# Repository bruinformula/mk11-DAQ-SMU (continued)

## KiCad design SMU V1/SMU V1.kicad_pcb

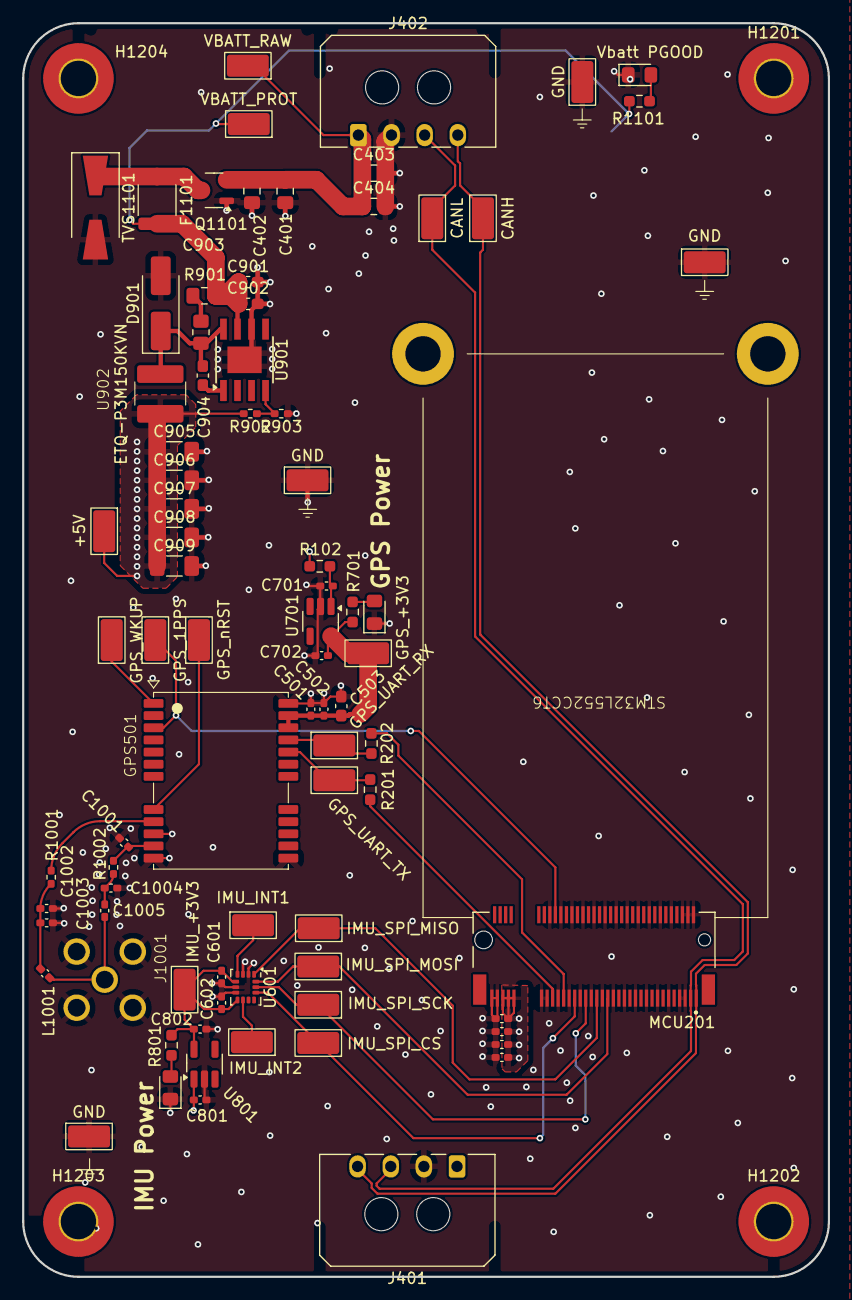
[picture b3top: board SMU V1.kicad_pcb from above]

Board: 4 copper layers, 72.9 x 113.5 mm, 86 parts (0 on the bottom side), 35 nets.

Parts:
C201, C202, C203, C204, C502, C601, C602, C1002: 100n; C_0402_1005Metric_Pad0.74x0.62mm_HandSolder
C401, C402, C403, C404: 22u; C_0805_2012Metric_Pad1.18x1.45mm_HandSolder
C501: 33p; C_0402_1005Metric_Pad0.74x0.62mm_HandSolder
C503: 4.7u; C_0603_1608Metric_Pad1.08x0.95mm_HandSolder
C701, C702, C801, C802: 2.2u; C_0402_1005Metric_Pad0.74x0.62mm_HandSolder
C901, C902: 22u; C_0603_1608Metric_Pad1.08x0.95mm_HandSolder
C903: 1.8p; C_0805_2012Metric_Pad1.18x1.45mm_HandSolder
C904: 10n; C_0603_1608Metric_Pad1.08x0.95mm_HandSolder
C905, C906, C907, C908, C909: 100u; C_1206_3216Metric_Pad1.33x1.80mm_HandSolder
C1001, C1003, C1004, C1005: 100p; C_0402_1005Metric_Pad0.74x0.62mm_HandSolder
D701, D801: GPS Power; D_0805_2012Metric_Pad1.15x1.40mm_HandSolder
D901: 550m; D_SMA_Handsoldering
D1101: Vbatt PGOOD; D_0805_2012Metric_Pad1.15x1.40mm_HandSolder
F1101: 500mA; Fuse_1812_4532Metric
GPS501: LC29HEAMD; Quectel LC49
H1201, H1202, H1203, H1204: MountingHole_Pad; MountingHole_3.2mm_M3_Pad_TopBottom
J401, J402: Connector; Molex_Micro-Fit_3.0_43650-0400_1x04_P3.00mm_Horizontal
J1001: SMA; THT SMA
L1001: 68n; L_0402_1005Metric_Pad0.77x0.64mm_HandSolder
MCU201: Krill; TE_1-2199119-5
Q1101: SI2301CDS-T1-GE3; SOT-23-3
R102, R201, R202: 0; R_0603_1608Metric_Pad0.98x0.95mm_HandSolder
R701, R801: 120; R_0603_1608Metric_Pad0.98x0.95mm_HandSolder
R901: 180k; R_0805_2012Metric_Pad1.20x1.40mm_HandSolder
R902: 10k; R_0402_1005Metric_Pad0.72x0.64mm_HandSolder
R903: 3.3k; R_0402_1005Metric_Pad0.72x0.64mm_HandSolder
R1001: 10; R_0402_1005Metric_Pad0.72x0.64mm_HandSolder
R1002: 0; R_0402_1005Metric_Pad0.72x0.64mm_HandSolder
R1101: 1.8k; R_0603_1608Metric_Pad0.98x0.95mm_HandSolder
TP205: CANH; TestPoint_Keystone_5019_Miniature
TP206: CANL; TestPoint_Keystone_5019_Miniature
TP301: VBATT_RAW; TestPoint_Keystone_5019_Miniature
TP302: VBATT_PROT; TestPoint_Keystone_5019_Miniature
TP303: +5V; TestPoint_Keystone_5019_Miniature
TP305, TP306, TP307, TP308: GND; TestPoint_Keystone_5019_Miniature
TP501: GPS_UART_RX; TestPoint_Keystone_5019_Miniature
TP502: GPS_UART_TX; TestPoint_Keystone_5019_Miniature
TP503: GPS_WKUP; TestPoint_Keystone_5019_Miniature
TP504: GPS_1PPS; TestPoint_Keystone_5019_Miniature
TP505: GPS_nRST; TestPoint_Keystone_5019_Miniature
TP506: GPS_+3V3; TestPoint_Keystone_5019_Miniature
TP601: IMU_+3V3; TestPoint_Keystone_5019_Miniature
TP602: IMU_INT2; TestPoint_Keystone_5019_Miniature
TP603: IMU_INT1; TestPoint_Keystone_5019_Miniature
TP604: IMU_SPI_CS; TestPoint_Keystone_5019_Miniature
TP605: IMU_SPI_MISO; TestPoint_Keystone_5019_Miniature
TP606: IMU_SPI_MOSI; TestPoint_Keystone_5019_Miniature
TP607: IMU_SPI_SCK; TestPoint_Keystone_5019_Miniature
TVS1101: 16Vrwm; D_SMA-SMB_Universal_Handsoldering
U601: LSM6DSOTR; LGA-14_3x2.5mm_P0.5mm_LayoutBorder3x4y
U701, U801: TPS7A2033PDBVR; SOT-23-5_HandSoldering
U901: TPS5430DDAR; TI_SO-PowerPAD-8
U902: ETQ-P3M150KVN; BWVS005050404R7M00

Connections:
+5V: C201.1, C202.1, C203.1, C204.1, C801.1, C905.1, C906.1, C907.1, C908.1, C909.1, MCU201.67 (5V), MCU201.69 (5V), MCU201.71 (5V), R102.2, R902.2, TP303.1, U801.1 (VIN), U902.2
/Antenna/ANT_OUT_RF: C1005.2, J1001.1, L1001.1
/Antenna/GPS_ANT_RF: C1001.1, GPS501.11 (RF_IN), R1002.1
/Antenna/GPS_ANT_RF_R: C1004.1, C1005.1, R1002.2
/Antenna/GPS_RF_VDD: GPS501.9 (VDD_RF), R1001.1
/Antenna/GPS_RF_VDD_R: C1002.1, C1003.1, L1001.2, R1001.2
/CAN+: J401.4 (CANH), J402.4 (CANH), MCU201.1 (MCU_CAN+), TP205.1
/CAN-: J401.3 (CANL), J402.3 (CANL), MCU201.3 (MCU_CAN-), TP206.1
/GPS/GPS_1PPS: GPS501.3 (1PPS), MCU201.52 (PB0), TP504.1
/GPS/GPS_UART.RX: GPS501.21 (UART_RXD), R202.2, TP501.1
/GPS/GPS_UART.TX: GPS501.20 (UART_TXD), R201.2, TP502.1
/GPS/GPS_WKUP: GPS501.1 (WAKEUP), TP503.1
/GPS/GPS_nRST: GPS501.8 (RESET_N), TP505.1
/GPS/PP3300_GPS_VCC: C501.1, C502.1, C503.1, C702.1, GPS501.22 (V_BCKUP), GPS501.23 (VCC), R701.1, TP506.1, U701.5 (VOUT)
/GPS/PP5000_GPS_VSUPP: C701.1, R102.1, U701.1 (VIN)
/IMU/IMU_INT1: TP603.1, U601.4 (INT1)
/IMU/IMU_INT2: TP602.1, U601.9 (INT2)
/IMU/PP3300_IMU_VDD: C601.1, C602.1, C802.1, R801.1, TP601.1, U601.5 (VDDIO), U601.8 (VDD), U801.5 (VOUT)
/IMU_SPI.CS: MCU201.45 (SPI1_NSS), TP604.1, U601.12 (CS)
/IMU_SPI.MISO: MCU201.37 (SPI1_MISO), TP605.1, U601.1 (SPI_MISO)
/IMU_SPI.MOSI: MCU201.33 (SPI1_MOSI), TP606.1, U601.14 (4W_SPI_MOSI)
/IMU_SPI.SCK: MCU201.41 (SPI1_SCK), TP607.1, U601.13 (SPI_SCK)
/Main IO/VBATT+: C401.1, C402.1, C403.1, C404.1, J401.1 (VBATT+), J402.1 (VBATT+), Q1101.2 (S), TP301.1
/Power/5V Buck/BUCK_VSENSE: R902.1, R903.2, U901.4 (VSENSE)
/Power/5V Buck/PPVAR_VBATT_PROT: C901.1, C902.1, C903.1, F1101.2, R1101.1, TP302.1, U901.7 (VIN)
/Power/5V Buck/Rsnub: C903.2, R901.1
/Power/5V Buck/SWITCH_NODE: C904.2, D901.1 (K), R901.2, U901.8 (PH), U902.1
GND: C201.2, C202.2, C203.2, C204.2, C401.2, C402.2, C403.2, C404.2, C501.2, C502.2, C503.2, C601.2, C602.2, C701.2, C702.2, C801.2, C802.2, C901.2, C902.2, C905.2, C906.2, C907.2, C908.2, C909.2, C1001.2, C1002.2, C1003.2, C1004.2, D701.1 (K), D801.1 (K), D901.2 (A), D1101.1 (K), GPS501.10 (GND), GPS501.12 (GND), GPS501.13 (GND), GPS501.24 (GND), J401.2 (GND), J402.2 (GND), J1001.2, MCU201.2 (GND), MCU201.4 (GND), MCU201.5 (GND), MCU201.6 (GND), MCU201.7 (GND), MCU201.10 (GND), MCU201.11 (GND), MCU201.14 (GND), MCU201.15 (GND), MCU201.18 (GND), MCU201.19 (GND), MCU201.22 (GND), MCU201.23 (GND), MCU201.26 (GND), MCU201.27 (GND), MCU201.30 (GND), MCU201.31 (GND), MCU201.34 (GND), MCU201.35 (GND), MCU201.38 (GND), MCU201.39 (GND), MCU201.42 (GND), MCU201.43 (GND), MCU201.46 (GND), MCU201.47 (GND), MCU201.50 (GND), MCU201.51 (GND), MCU201.54 (GND), MCU201.55 (GND), MCU201.57 (GND), MCU201.73 (GND), MCU201.75 (GND), Q1101.1 (G), R903.1, TP305.1, TP306.1, TP307.1, TP308.1, TVS1101.2, U601.2 (SDx), U601.3 (SCx), U601.6 (GND), U601.7 (GND), U701.2 (GND), U801.2 (GND), U901.6 (GND), U901.9 (GNDPAD)
unnamed: D701.2 (A), R701.2
unnamed: D801.2 (A), R801.2
unnamed: D1101.2 (A), R1101.2
unnamed: MCU201.53 (UART4_TX), R201.1
unnamed: MCU201.49 (UART4_RX), R202.1
unnamed: F1101.1, Q1101.3 (D), TVS1101.1
unnamed: C904.1, U901.1 (BOOT)

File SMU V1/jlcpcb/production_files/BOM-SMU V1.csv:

Comment,Designator,Footprint,LCSC,Quantity
+5V,TP303,TestPoint_Keystone_5019_Miniature,C5199800,1
0,R1002,R_0402_1005Metric_Pad0.72x0.64mm_HandSolder,C17168,1
0,"R102,R201,R202",R_0603_1608Metric_Pad0.98x0.95mm_HandSolder,C21189,3
1.8k,R1101,R_0603_1608Metric_Pad0.98x0.95mm_HandSolder,C4177,1
1.8p,C903,C_0805_2012Metric_Pad1.18x1.45mm_HandSolder,C376870,1
10,R1001,R_0402_1005Metric_Pad0.72x0.64mm_HandSolder,C25077,1
100n,"C201,C202,C203,C204,C502,C601,C602",C_0402_1005Metric_Pad0.74x0.62mm_HandSolder,C1525,7
100n,C1002,C_0402_1005Metric_Pad0.74x0.62mm_HandSolder,C307331,1
100p,"C1003,C1005",C_0402_1005Metric_Pad0.74x0.62mm_HandSolder,C1546,2
100u,"C905,C906,C907,C908,C909",C_1206_3216Metric_Pad1.33x1.80mm_HandSolder,C15008,5
10k,R902,R_0402_1005Metric_Pad0.72x0.64mm_HandSolder,C25744,1
10n,C904,C_0603_1608Metric_Pad1.08x0.95mm_HandSolder,C57112,1
120,"R701,R801",R_0603_1608Metric_Pad0.98x0.95mm_HandSolder,C22787,2
16Vrwm,TVS1101,D_SMA-SMB_Universal_Handsoldering,C19077571,1
180k,R901,R_0805_2012Metric_Pad1.20x1.40mm_HandSolder,C17501,1
2.2u,"C701,C702,C801,C802",C_0402_1005Metric_Pad0.74x0.62mm_HandSolder,C12530,4
22u,"C401,C402,C403,C404",C_0805_2012Metric_Pad1.18x1.45mm_HandSolder,C45783,4
22u,"C901,C902",C_0603_1608Metric_Pad1.08x0.95mm_HandSolder,C59461,2
3.3k,R903,R_0402_1005Metric_Pad0.72x0.64mm_HandSolder,C25890,1
33p,C501,C_0402_1005Metric_Pad0.74x0.62mm_HandSolder,C1562,1
4.7u,C503,C_0603_1608Metric_Pad1.08x0.95mm_HandSolder,C19666,1
500mA,F1101,Fuse_1812_4532Metric,C3762102,1
550m,D901,D_SMA_Handsoldering,C22452,1
68n,L1001,L_0402_1005Metric_Pad0.77x0.64mm_HandSolder,C2044127,1
CANH,TP205,TestPoint_Keystone_5019_Miniature,C5199800,1
CANL,TP206,TestPoint_Keystone_5019_Miniature,C5199800,1
ETQ-P3M150KVN,U902,BWVS005050404R7M00,C3223274,1
GND,"TP305,TP306,TP307,TP308",TestPoint_Keystone_5019_Miniature,C5199800,4
GPS Power,"D701,D801",D_0805_2012Metric_Pad1.15x1.40mm_HandSolder,C2297,2
GPS_+3V3,TP506,TestPoint_Keystone_5019_Miniature,C5199800,1
GPS_1PPS,TP504,TestPoint_Keystone_5019_Miniature,C5199800,1
GPS_UART_RX,TP501,TestPoint_Keystone_5019_Miniature,C5199800,1
GPS_UART_TX,TP502,TestPoint_Keystone_5019_Miniature,C5199800,1
GPS_WKUP,TP503,TestPoint_Keystone_5019_Miniature,C5199800,1
GPS_nRST,TP505,TestPoint_Keystone_5019_Miniature,C5199800,1
IMU_+3V3,TP601,TestPoint_Keystone_5019_Miniature,C5199800,1
IMU_INT1,TP603,TestPoint_Keystone_5019_Miniature,C5199800,1
IMU_INT2,TP602,TestPoint_Keystone_5019_Miniature,C5199800,1
IMU_SPI_CS,TP604,TestPoint_Keystone_5019_Miniature,C5199800,1
IMU_SPI_MISO,TP605,TestPoint_Keystone_5019_Miniature,C5199800,1
IMU_SPI_MOSI,TP606,TestPoint_Keystone_5019_Miniature,C5199800,1
IMU_SPI_SCK,TP607,TestPoint_Keystone_5019_Miniature,C5199800,1
LSM6DSOTR,U601,LGA-14_3x2.5mm_P0.5mm_LayoutBorder3x4y,C481766,1
SI2301CDS-T1-GE3,Q1101,SOT-23-3,C10487,1
SMA,J1001,THT SMA,C5199904,1
TPS5430DDAR,U901,TI_SO-PowerPAD-8,C9864,1
VBATT_PROT,TP302,TestPoint_Keystone_5019_Miniature,C5199800,1
VBATT_RAW,TP301,TestPoint_Keystone_5019_Miniature,C5199800,1
Vbatt PGOOD,D1101,D_0805_2012Metric_Pad1.15x1.40mm_HandSolder,C2297,1
Connector,J402,Molex_Micro-Fit_3.0_43650-0400_1x04_P3.00mm_Horizontal,,1
TPS7A2033PDBVR,U801,SOT-23-5_HandSoldering,,1
LC29HEAMD,GPS501,Quectel LC49,,1
TPS7A2033PDBVR,U701,SOT-23-5_HandSoldering,,1
Connector,J401,Molex_Micro-Fit_3.0_43650-0400_1x04_P3.00mm_Horizontal,,1
Krill,MCU201,TE_1-2199119-5,,1

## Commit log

2025-12-24 i forget what i changed
2026-01-14 halfway done with routing, still needs antenna
2026-01-15 finished, should prob double check the high frequency stuff
2026-01-21 sync
2026-02-13 exported gerbers
2026-04-22 v2 layout
2026-04-22 test
2026-05-11 improved V3
    added uart/spi test points and status leds
    removed main 3v3 ldo
    added silkscreen
2026-05-11 fixed mounting holes
2026-05-11 actual final v3
